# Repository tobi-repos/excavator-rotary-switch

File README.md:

# excavator-rotary-switch
Rotary switch to control operating modes.

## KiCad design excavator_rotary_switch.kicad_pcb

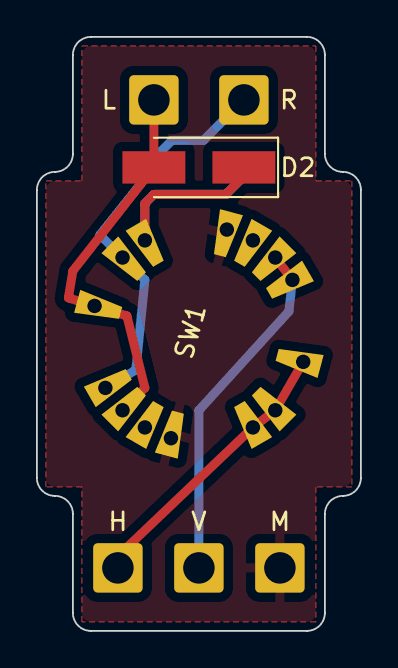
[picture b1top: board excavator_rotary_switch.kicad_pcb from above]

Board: 2 copper layers, 18.0 x 33.0 mm, 8 parts (1 on the bottom side), 6 nets.

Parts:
D1, D2: S 1G SMD; D_SMA_Handsoldering
H: BACK; SolderWire-1sqmm_1x01_D1.4mm_OD2.7mm
L: LEFT; SolderWire-1sqmm_1x01_D1.4mm_OD2.7mm
M: GROUND; SolderWire-1sqmm_1x01_D1.4mm_OD2.7mm
R: RIGHT; SolderWire-1sqmm_1x01_D1.4mm_OD2.7mm
SW1: MRK206
V: FRONT; SolderWire-1sqmm_1x01_D1.4mm_OD2.7mm

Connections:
unnamed: D1.1 (K), D2.1 (K), SW1.12
unnamed: D1.2 (A), R.1, SW1.9, SW1.11
unnamed: D2.2 (A), L.1, SW1.8, SW1.10
unnamed: M.1, SW1.13, SW1.14
unnamed: SW1.2, SW1.3, V.1
unnamed: H.1, SW1.4, SW1.5, SW1.6

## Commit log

2023-08-16 Added all project files.
